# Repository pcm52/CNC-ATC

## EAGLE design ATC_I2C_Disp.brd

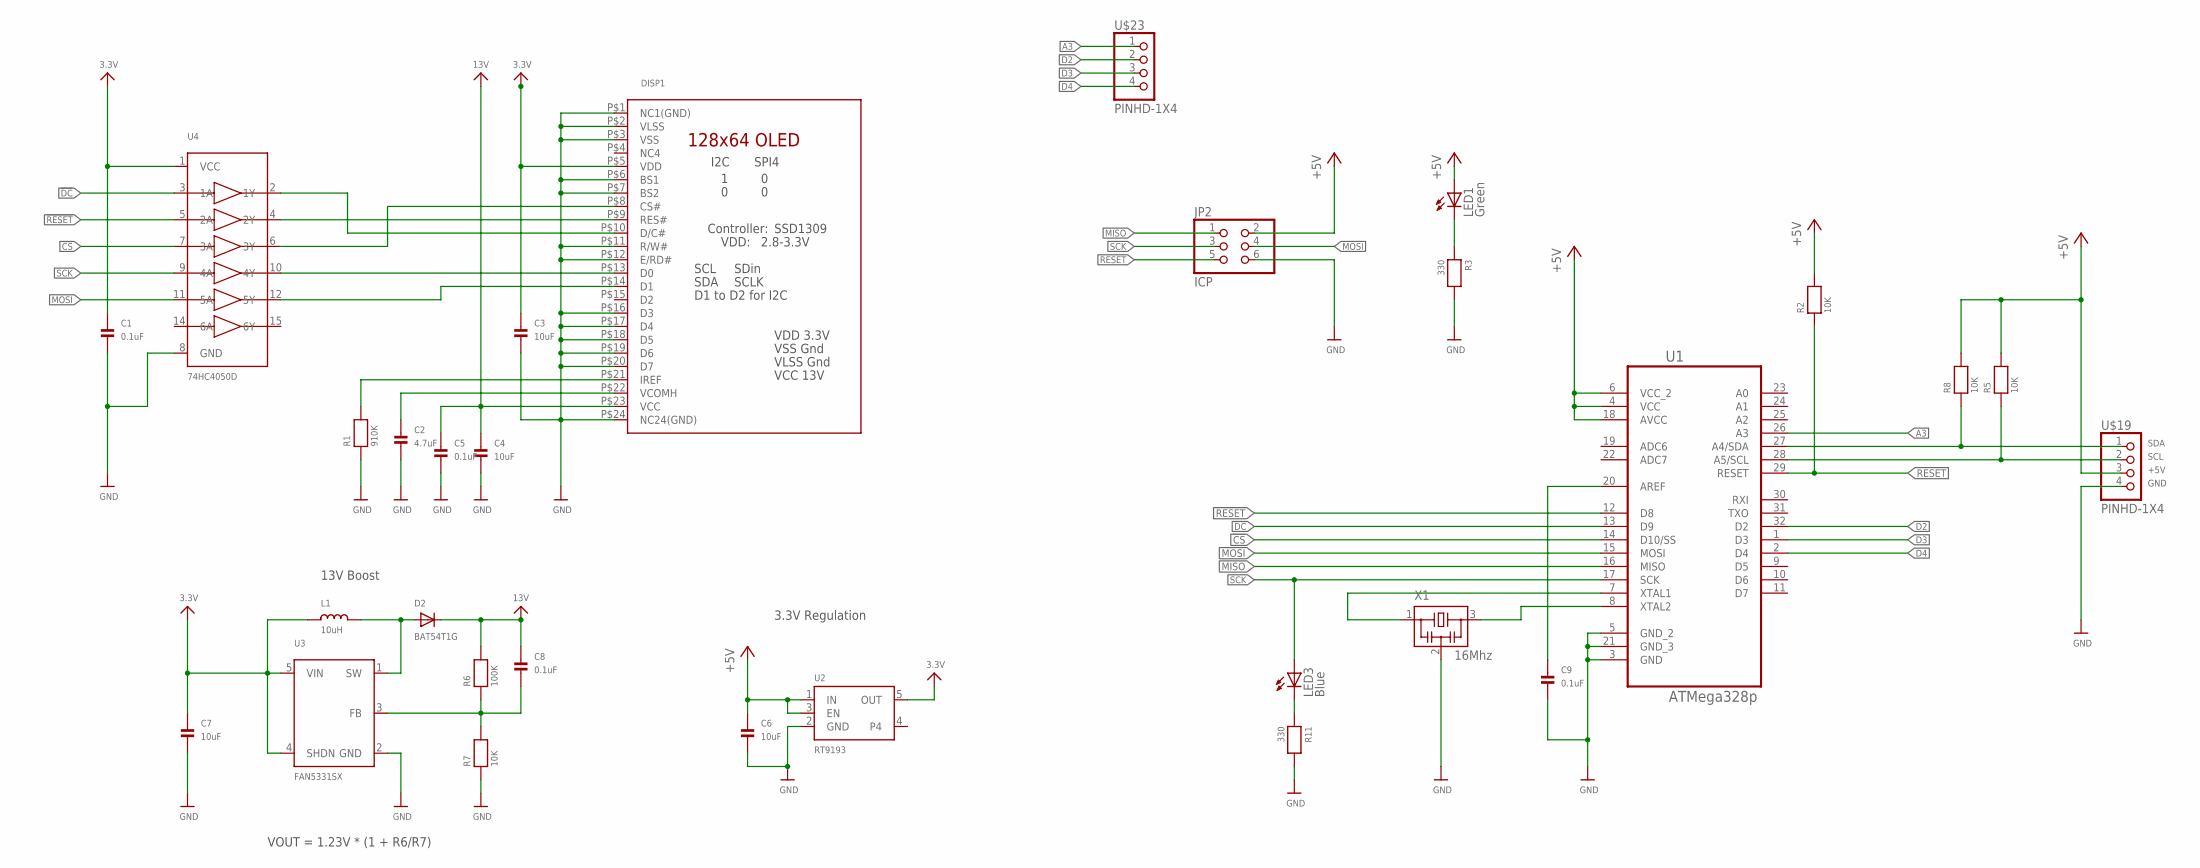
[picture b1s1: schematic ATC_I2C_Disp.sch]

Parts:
C1, C5, C8, C9: 0.1uF; 0805
C2: 4.7uF; 0805
C3, C4, C6, C7: 10uF; 0805
D2: BAT54T1G; SOD-123
DISP1: 1.5-128X64-OLED; 1.5-128X64-TOP-CONTACT
JP2: ICP; 2X03
L1: 10uH; INDUCTOR_1007
LED1: Green; CHIPLED_0805
LED3: Blue; CHIPLED_0805
R1: 910K; 0805
R2, R5, R7, R8: 10K; 0805
R3, R11: 330; 0805
R6: 100K; 0805
U1: ATMega328p; TQFP-32
U2: RT9193; SOT23-5
U3: FAN5331SX; SOT23-5
U4: 74HC4050D; SOIC16
U$19, U$23: PINHD-1X4; 1X04-BIG
X1: 16Mhz; CSTCE-CRYSTAL-OSC

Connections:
3.3V: C1.1, C3.1, C7.1, DISP1.P$5 (VDD), L1.P$1 (1), U2.5 (OUT), U3.4 (SHDN), U3.5 (VIN), U4.1 (VCC)
13V: C4.1, C5.1, C8.1, D2.C, DISP1.P$23 (VCC), R6.2
!CS: U1.14 (D10/SS), U4.7 (3A)
!DC: U1.13 (D9), U4.3 (1A)
!RESET: U1.12 (D8), U4.5 (2A)
+5V: C6.1, JP2.2, LED1.A, R2.2, R5.2, R8.2, U1.4 (VCC), U1.6 (VCC_2), U1.18 (AVCC), U2.1 (IN), U2.3 (EN), U$19.3
A3: U1.26 (A3), U$23.1
CS: DISP1.P$8 (CS#), U4.6 (3Y)
D0: DISP1.P$13 (D0), U4.10 (4Y)
D1: DISP1.P$14 (D1), U4.12 (5Y)
D2: U1.32 (D2), U$23.2
D3: U1.1 (D3), U$23.3
D4: U1.2 (D4), U$23.4
DC: DISP1.P$10 (D/C#), U4.2 (1Y)
GND: C1.2, C2.2, C3.2, C4.2, C5.2, C6.2, C7.2, C9.2, DISP1.P$1 (NC1(GND)), DISP1.P$2 (VLSS), DISP1.P$3 (VSS), DISP1.P$6 (BS1), DISP1.P$7 (BS2), DISP1.P$11 (R/W#), DISP1.P$12 (E/RD#), DISP1.P$16 (D3), DISP1.P$17 (D4), DISP1.P$18 (D5), DISP1.P$19 (D6), DISP1.P$20 (D7), DISP1.P$24 (NC24(GND)), JP2.6, R1.1, R3.2, R7.1, R11.2, U1.3 (GND), U1.5 (GND_2), U1.21 (GND_3), U2.2 (GND), U3.2 (GND), U4.8 (GND), U$19.4, X1.2
MISO: JP2.1, U1.16 (MISO)
MOSI: JP2.4, U1.15 (MOSI), U4.11 (5A)
unnamed: LED1.C, R3.1
unnamed: D2.A, L1.P$2 (2), U3.1 (SW)
unnamed: U1.7 (XTAL1), X1.1
unnamed: DISP1.P$21 (IREF), R1.2
unnamed: C8.2, R6.1, R7.2, U3.3 (FB)
unnamed: C2.1, DISP1.P$22 (VCOMH)
unnamed: U1.8 (XTAL2), X1.3
unnamed: C9.1, U1.20 (AREF)
unnamed: LED3.C, R11.1
RES: DISP1.P$9 (RES#), U4.4 (2Y)
RESET: JP2.5, R2.1, U1.29 (RESET)
SCK: JP2.3, LED3.A, U1.17 (SCK), U4.9 (4A)
SCL: R5.1, U1.28 (A5/SCL), U$19.2
SDA: R8.1, U1.27 (A4/SDA), U$19.1

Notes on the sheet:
3.3V Regulation
VOUT = 1.23V * (1 + R6/R7)
13V Boost

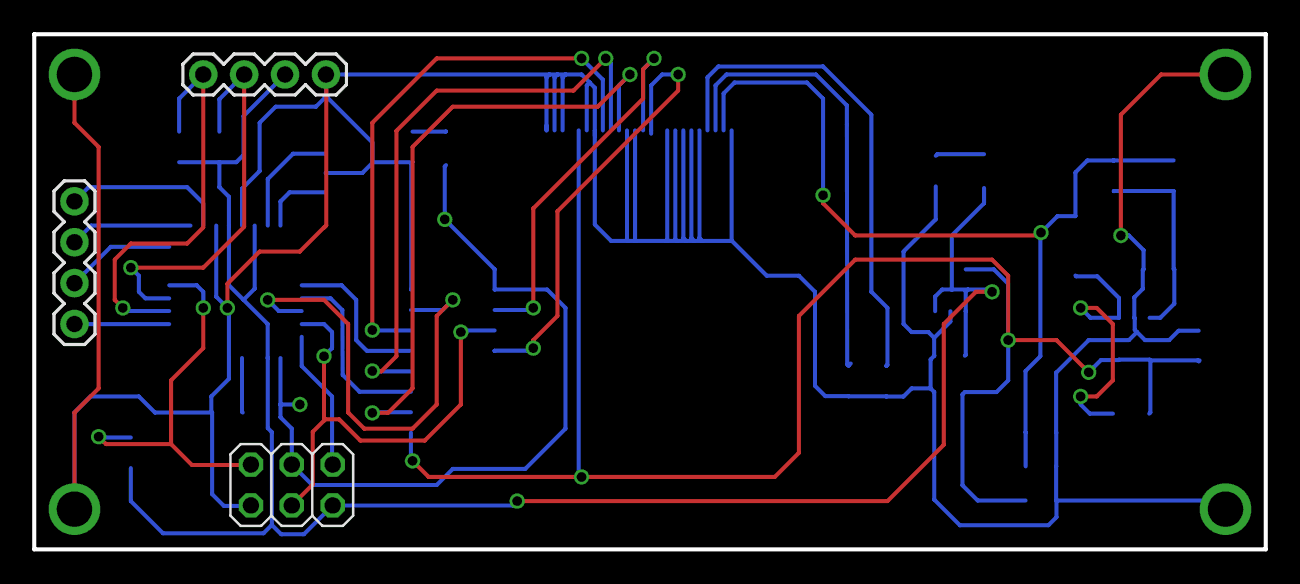
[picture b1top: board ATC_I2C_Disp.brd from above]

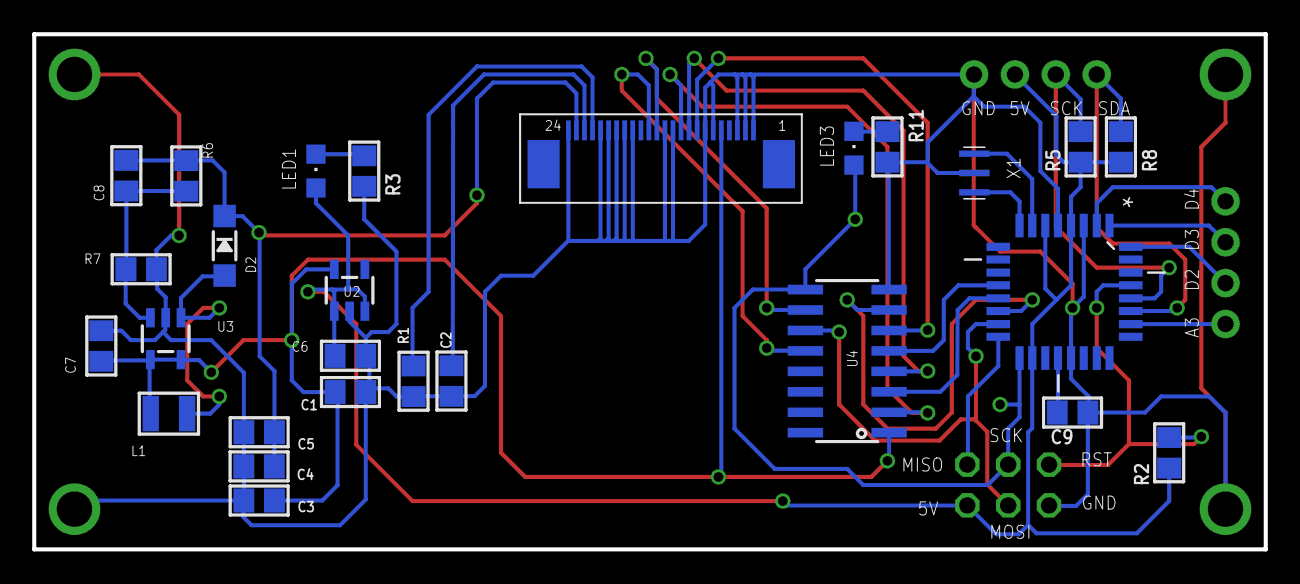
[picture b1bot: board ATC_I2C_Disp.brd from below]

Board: 2 copper layers, 76.5 x 32.0 mm, 30 parts (27 on the bottom side), 31 nets.

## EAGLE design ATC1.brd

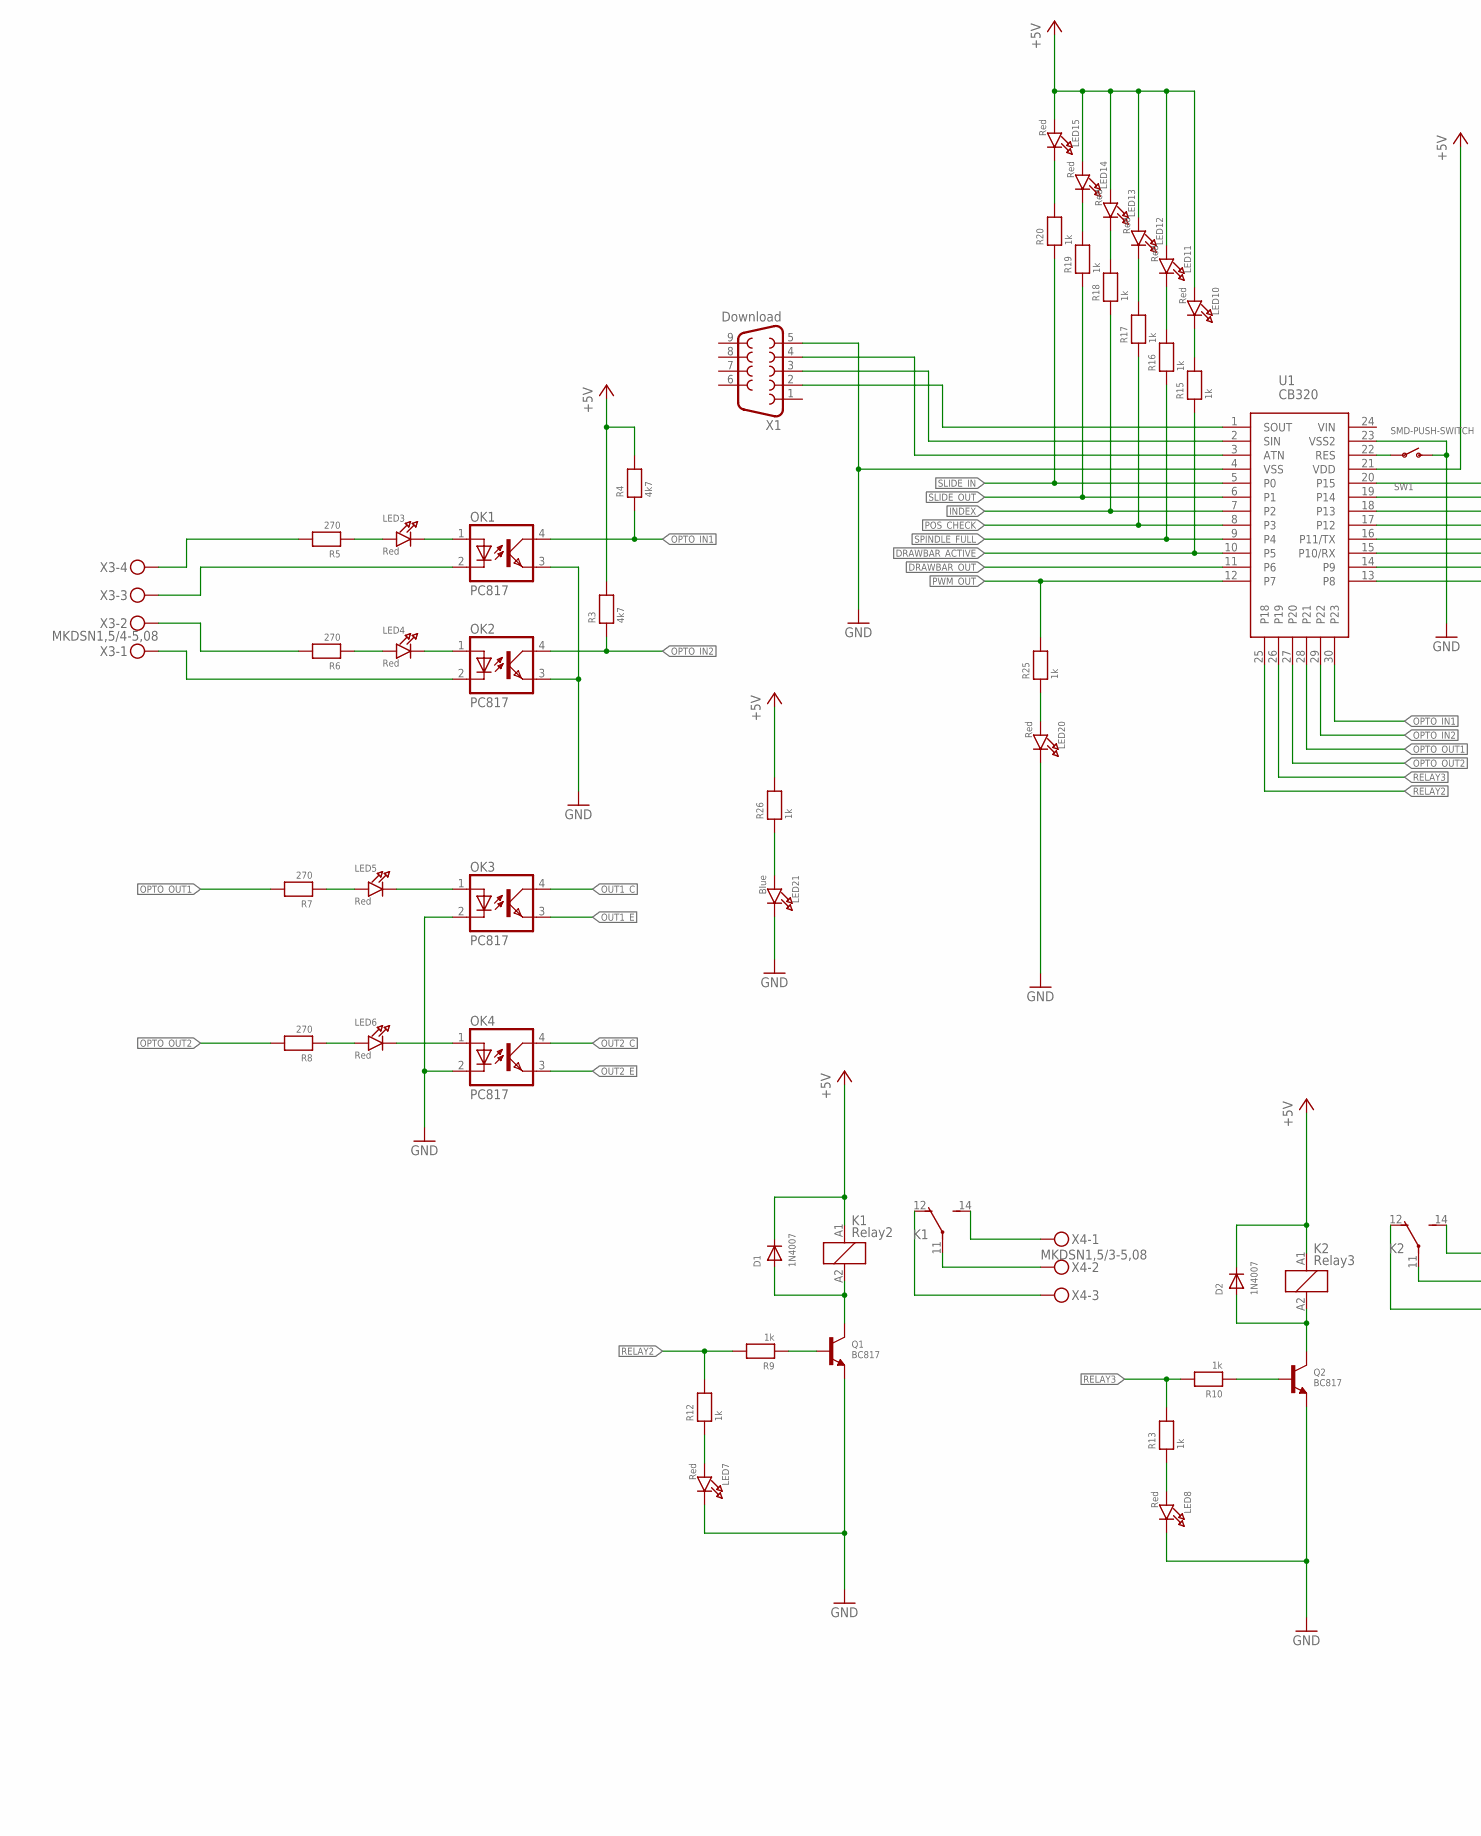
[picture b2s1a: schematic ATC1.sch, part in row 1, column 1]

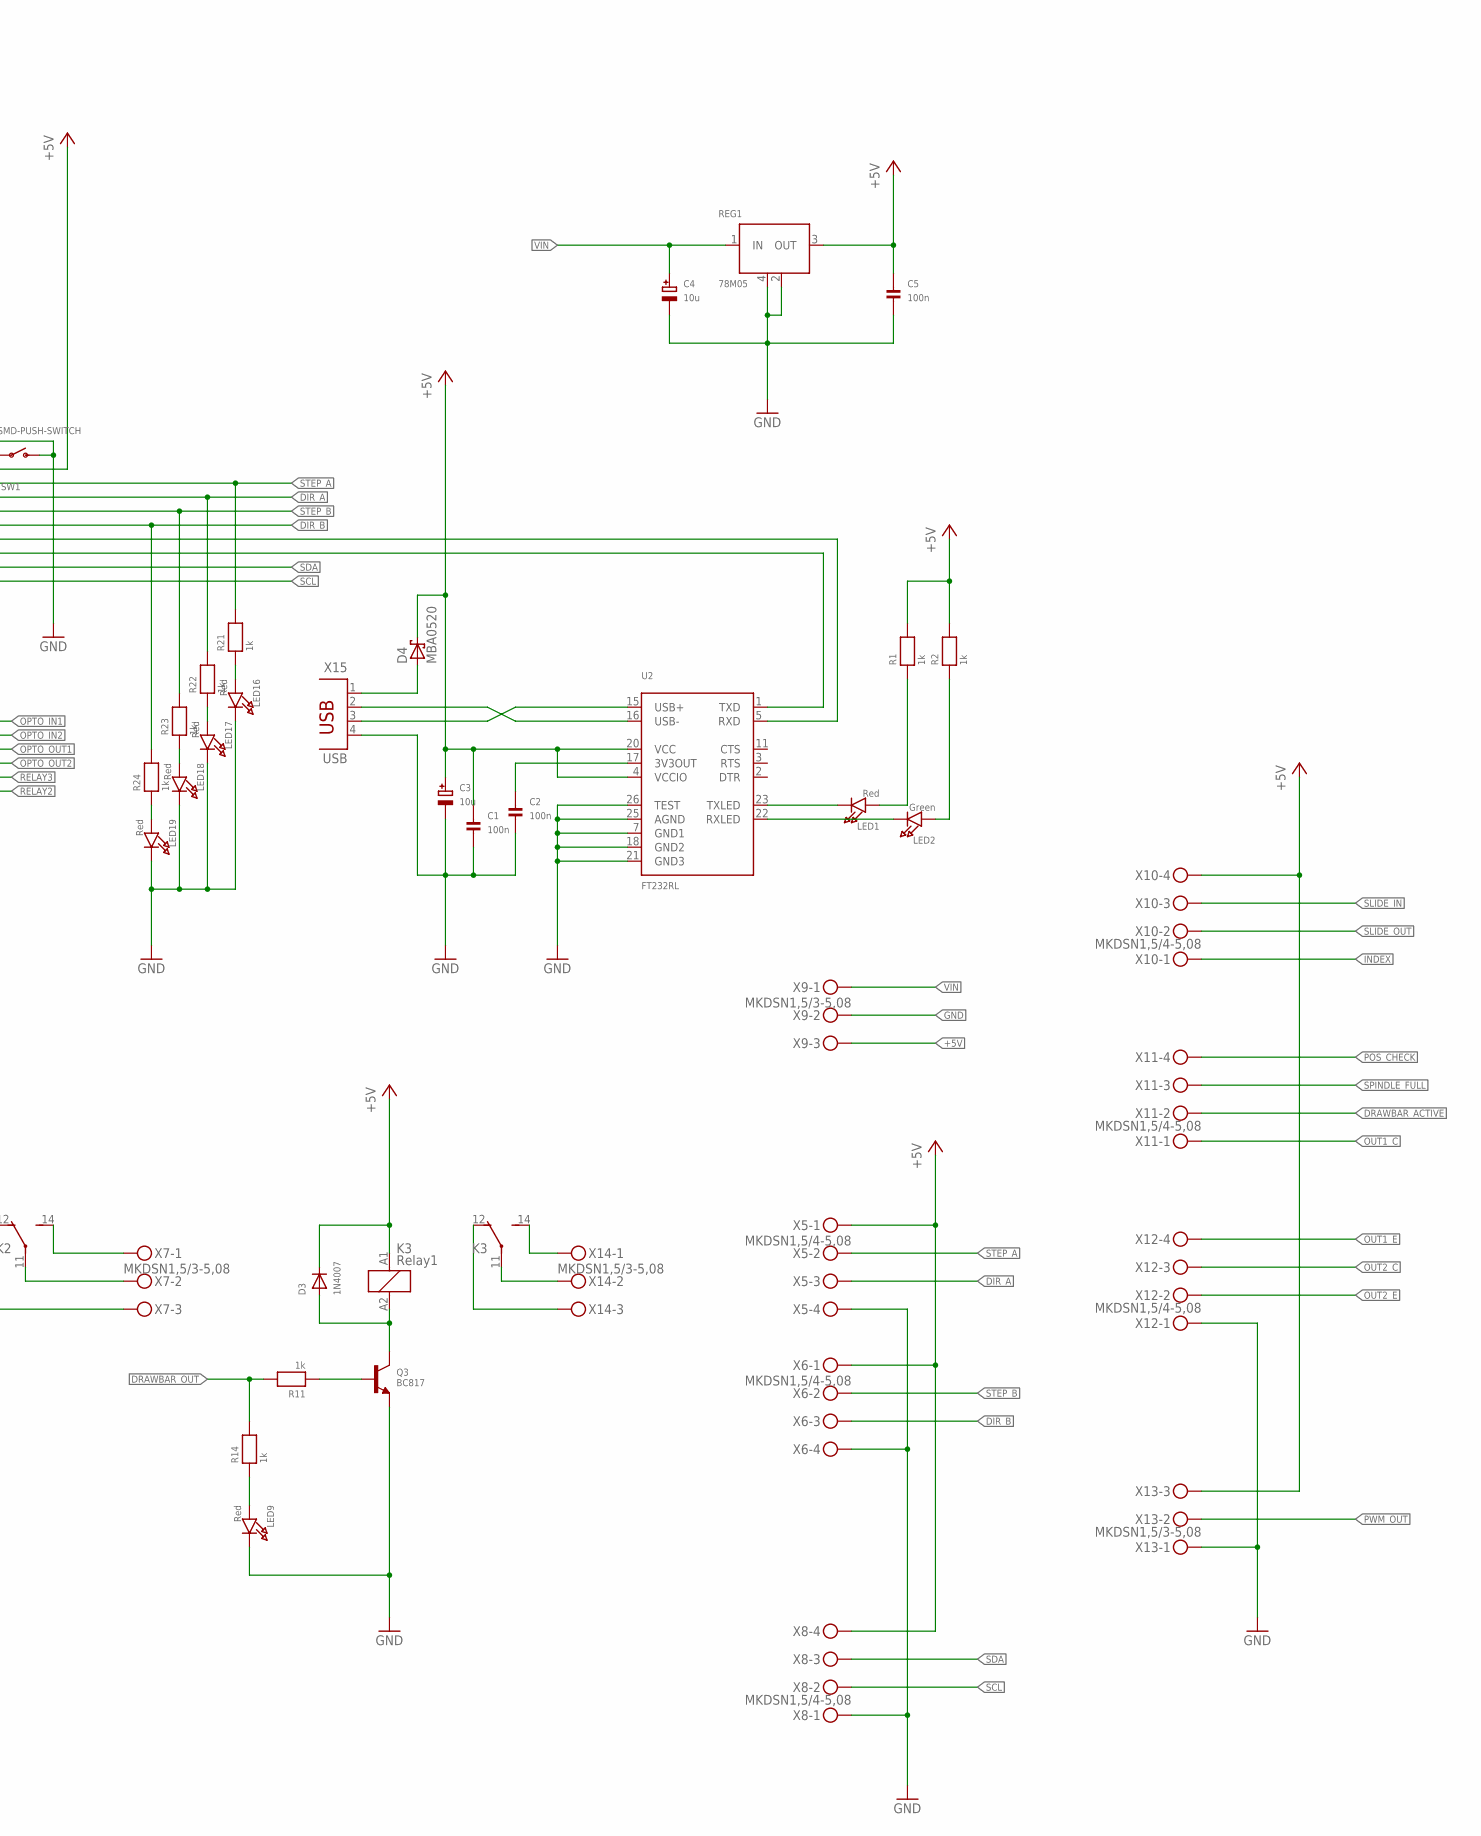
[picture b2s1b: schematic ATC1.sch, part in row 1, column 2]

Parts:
C1, C2, C5: 100n; 0805
C3, C4: 10u; EIA3216-18/A-R
D1, D2, D3: 1N4007; SOD-123
D4: MBA0520; SOD123
K1: Relay2; SRD
K2: Relay3; SRD
K3: Relay1; SRD
LED1, LED3, LED4, LED5, LED6, LED7, LED8, LED9, LED10, LED11, LED12, LED13, LED14, LED15, LED16, LED17, LED18, LED19, LED20: Red; CHIPLED_0805
LED2: Green; CHIPLED_0805
LED21: Blue; CHIPLED_0805
OK1, OK2, OK3, OK4: PC817; SM4-GW
Q1, Q2, Q3: BC817; SOT23-WIDE
R1, R2, R9, R10, R11, R12, R13, R14, R15, R16, R17, R18, R19, R20, R21, R22, R23, R24, R25, R26: 1k; 0805
R3, R4: 4k7; 0805
R5, R6, R7, R8: 270; 0805
REG1: 78M05; UA78M05
SW1: SMD-PUSH-SWITCH; PUSH-BUTTON-SMD
U1: CB320; DIL24
U2: FT232RL; SSOP28DB
X1: Download; F09HP
X3, X5, X6, X8, X10, X11, X12: MKDSN1,5/4-5,08
X4, X7, X9, X13, X14: MKDSN1,5/3-5,08
X15: USB; PN61729

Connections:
+5V: C1.1, C3.+, C5.1, D1.C, D2.C, D3.C, D4.C, K1.A1 (1), K2.A1 (1), K3.A1 (1), LED10.A, LED11.A, LED12.A, LED13.A, LED14.A, LED15.A, R1.2, R2.2, R3.2, R4.2, R26.2, REG1.3 (OUT), U1.21 (VDD), U2.4 (VCCIO), U2.20 (VCC), X5.1, X6.1, X8.4, X9.3, X10.4, X13.3
DIR_A: R22.2, U1.19 (P14), X5.3
DIR_B: R24.2, U1.17 (P12), X6.3
DRAWBAR_ACTIVE: R15.1, U1.10 (P5), X11.2
DRAWBAR_OUT: R11.2, R14.2, U1.11 (P6)
GND: C1.2, C2.2, C3.-, C4.-, C5.2, LED7.C, LED8.C, LED9.C, LED16.C, LED17.C, LED18.C, LED19.C, LED20.C, LED21.C, OK1.3 (EMIT), OK2.3 (EMIT), OK3.2 (C), OK4.2 (C), Q1.2 (E), Q2.2 (E), Q3.2 (E), REG1.2 (COMMON1), REG1.4 (COMMON2), SW1.P$2 (S), U1.4 (VSS), U1.23 (VSS2), U2.7 (GND1), U2.18 (GND2), U2.21 (GND3), U2.25 (AGND), U2.26 (TEST), X1.5, X5.4, X6.4, X8.1, X9.2, X12.1, X13.1, X15.4
INDEX: R18.1, U1.7 (P2), X10.1
unnamed: U2.15 (USB+), X15.3
unnamed: U2.16 (USB-), X15.2
unnamed: U1.2 (SIN), X1.3
unnamed: C2.1, U2.17 (3V3OUT)
unnamed: LED3.C, OK1.1 (A)
unnamed: U1.1 (SOUT), X1.2
unnamed: LED2.C, U2.22 (RXLED)
unnamed: LED1.C, U2.23 (TXLED)
unnamed: LED1.A, R1.1
unnamed: LED2.A, R2.1
unnamed: LED3.A, R5.1
unnamed: U1.15 (P10/RX), U2.1 (TXD)
unnamed: U1.16 (P11/TX), U2.5 (RXD)
unnamed: U1.3 (ATN), X1.4
unnamed: R5.2, X3.4
unnamed: LED4.C, OK2.1 (A)
unnamed: LED4.A, R6.1
unnamed: R6.2, X3.2
unnamed: OK1.2 (C), X3.3
unnamed: OK2.2 (C), X3.1
unnamed: LED5.A, R7.1
unnamed: LED5.C, OK3.1 (A)
unnamed: LED6.A, R8.1
unnamed: LED6.C, OK4.1 (A)
unnamed: Q1.1 (B), R9.1
unnamed: Q2.1 (B), R10.1
unnamed: D2.A, K2.A2 (2), Q2.3 (C)
unnamed: D1.A, K1.A2 (2), Q1.3 (C)
unnamed: Q3.1 (B), R11.1
unnamed: D3.A, K3.A2 (2), Q3.3 (C)
unnamed: K3.14 (O), X14.1
unnamed: K3.11, X14.2
unnamed: K1.14 (O), X4.1
unnamed: K1.11, X4.2
unnamed: K1.12 (C), X4.3
unnamed: K2.11, X7.2
unnamed: K2.12 (C), X7.3
unnamed: K2.14 (O), X7.1
unnamed: K3.12 (C), X14.3
unnamed: D4.A, X15.1
unnamed: SW1.P$1, U1.22 (RES)
unnamed: LED9.A, R14.1
unnamed: LED8.A, R13.1
unnamed: LED7.A, R12.1
unnamed: LED10.C, R15.2
unnamed: LED11.C, R16.2
unnamed: LED12.C, R17.2
unnamed: LED13.C, R18.2
unnamed: LED14.C, R19.2
unnamed: LED15.C, R20.2
unnamed: LED19.A, R24.1
unnamed: LED20.A, R25.1
unnamed: LED17.A, R22.1
unnamed: LED18.A, R23.1
unnamed: LED16.A, R21.1
unnamed: LED21.A, R26.1
OPTO_IN1: OK1.4 (COL), R4.1, U1.30 (P23)
OPTO_IN2: OK2.4 (COL), R3.1, U1.29 (P22)
OPTO_OUT1: R7.2, U1.28 (P21)
OPTO_OUT2: R8.2, U1.27 (P20)
OUT1_C: OK3.4 (COL), X11.1
OUT1_E: OK3.3 (EMIT), X12.4
OUT2_C: OK4.4 (COL), X12.3
OUT2_E: OK4.3 (EMIT), X12.2
POS_CHECK: R17.1, U1.8 (P3), X11.4
PWM_OUT: R25.2, U1.12 (P7), X13.2
RELAY2: R9.2, R12.2, U1.25 (P18)
RELAY3: R10.2, R13.2, U1.26 (P19)
SCL: U1.13 (P8), X8.2
SDA: U1.14 (P9), X8.3
SLIDE_IN: R20.1, U1.5 (P0), X10.3
SLIDE_OUT: R19.1, U1.6 (P1), X10.2
SPINDLE_FULL: R16.1, U1.9 (P4), X11.3
STEP_A: R21.2, U1.20 (P15), X5.2
STEP_B: R23.2, U1.18 (P13), X6.2
VIN: C4.+, REG1.1 (IN), X9.1

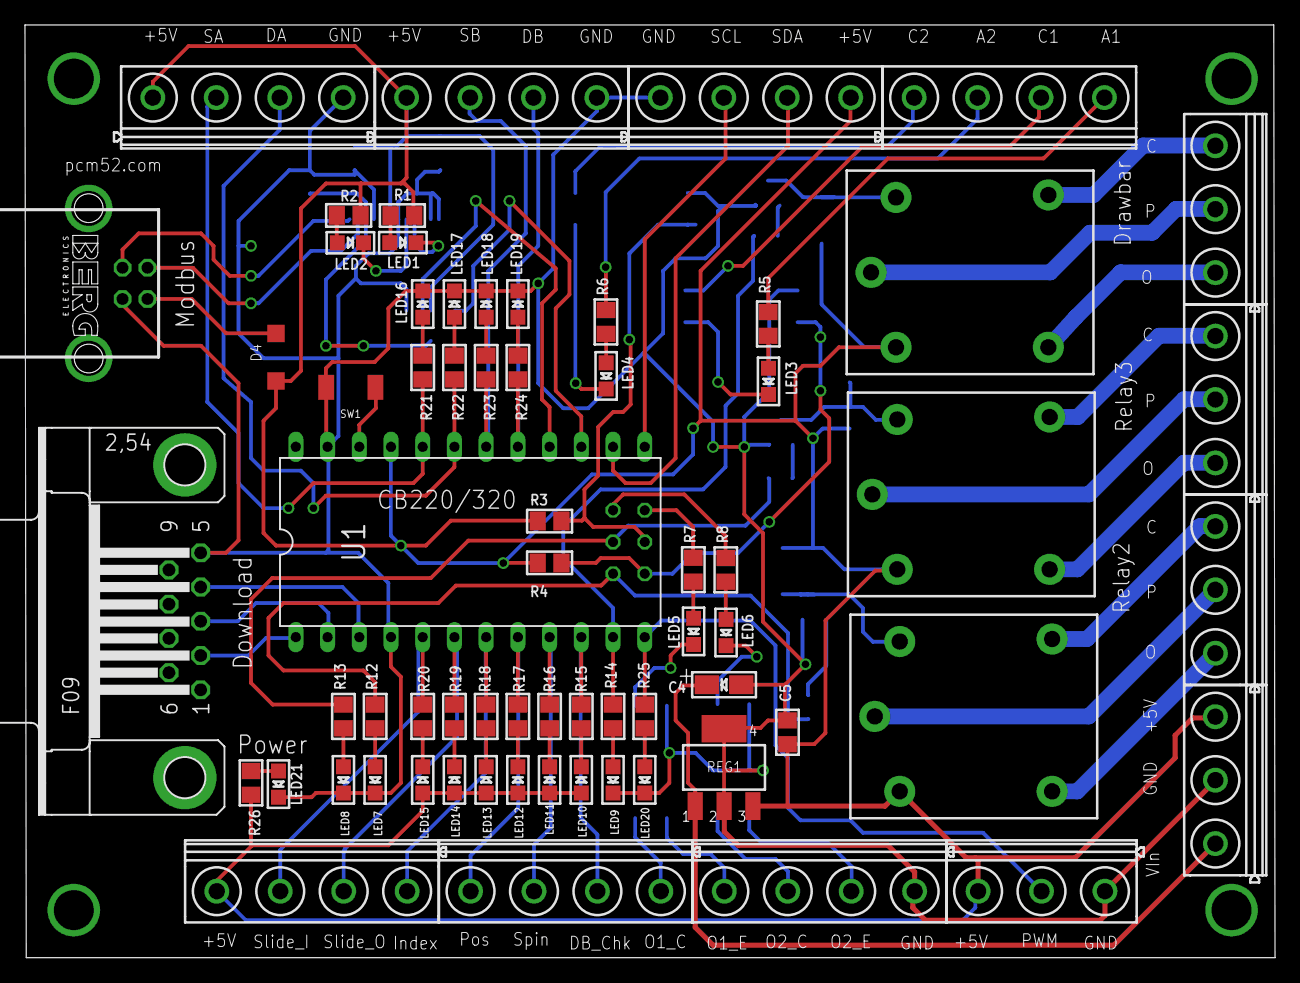
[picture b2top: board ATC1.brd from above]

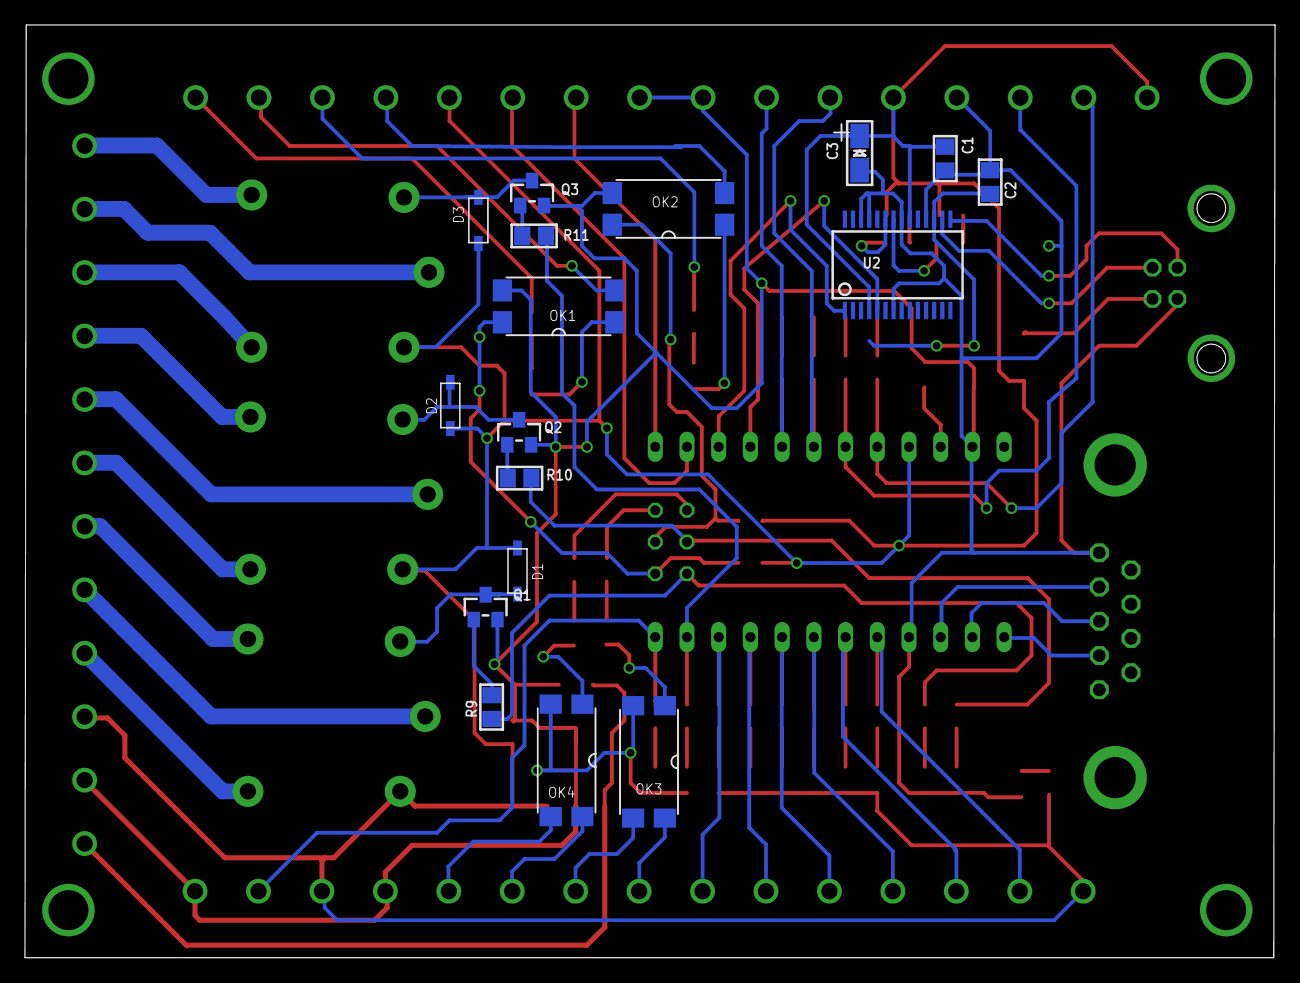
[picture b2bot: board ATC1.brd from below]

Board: 2 copper layers, 100.1 x 74.7 mm, 84 parts (17 on the bottom side), 83 nets.

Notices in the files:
parts and their libraries:
microbuilder: This work is placed in the public domain, and may be freely used for commercial and non-commercial work with the following conditions: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
